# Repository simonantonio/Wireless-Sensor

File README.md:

Wireless Sensor Host Board
=========

This is a board used to implement wireless reporting of various sensors

Suggested Sensor Modules
---  

 - DHT22 - Temperature & Humidity  
 - TSOP4838 - IR Sensor (32khz carrier)  
 - Photo Resistor - Basic Light Levels  
 - Pulse Sensing - For use with hall effect sensors or weather stations such as [Spark Fun's Weather Station](https://www.sparkfun.com/products/8942)
 - BMP180 - Barometer & Temperature
 - Battery Voltage Monitoring
 
Results can then be transmitted to a receiver using a NRF24L01+ 

The board aims to be a low power long term sensor platform, potentially being powered from a LIPO battery directly or using a step down module such as the [Pololu Step Down Voltage Regulator](http://www.pololu.com/product/2097) 

Licensed Under the [Creative Commons Attribution-ShareAlike 3.0 Unported (CC-BY-SA 3.0)](https://creativecommons.org/licenses/by-sa/3.0/) and designed with the OSHW concepts in mind

 Intial Board Prototypes are being producted via the awesome service at [Dirty PCB's](http://dirtypcbs.com/)  
 Feel free to buy them [here](http://dirtypcbs.com/view.php?share=2637&accesskey=f92450b07b6b3961496835b5062594b2)  for $25.00USD

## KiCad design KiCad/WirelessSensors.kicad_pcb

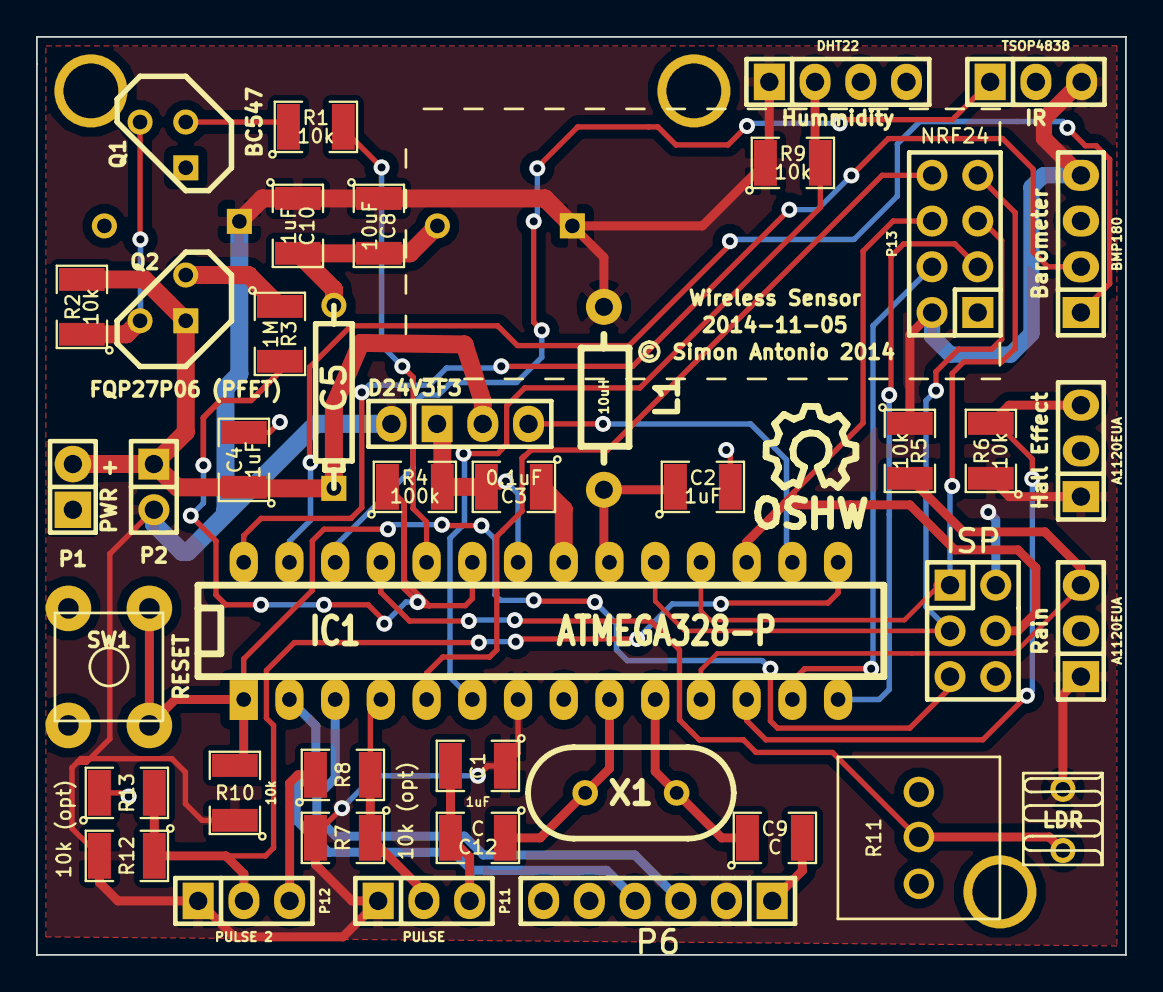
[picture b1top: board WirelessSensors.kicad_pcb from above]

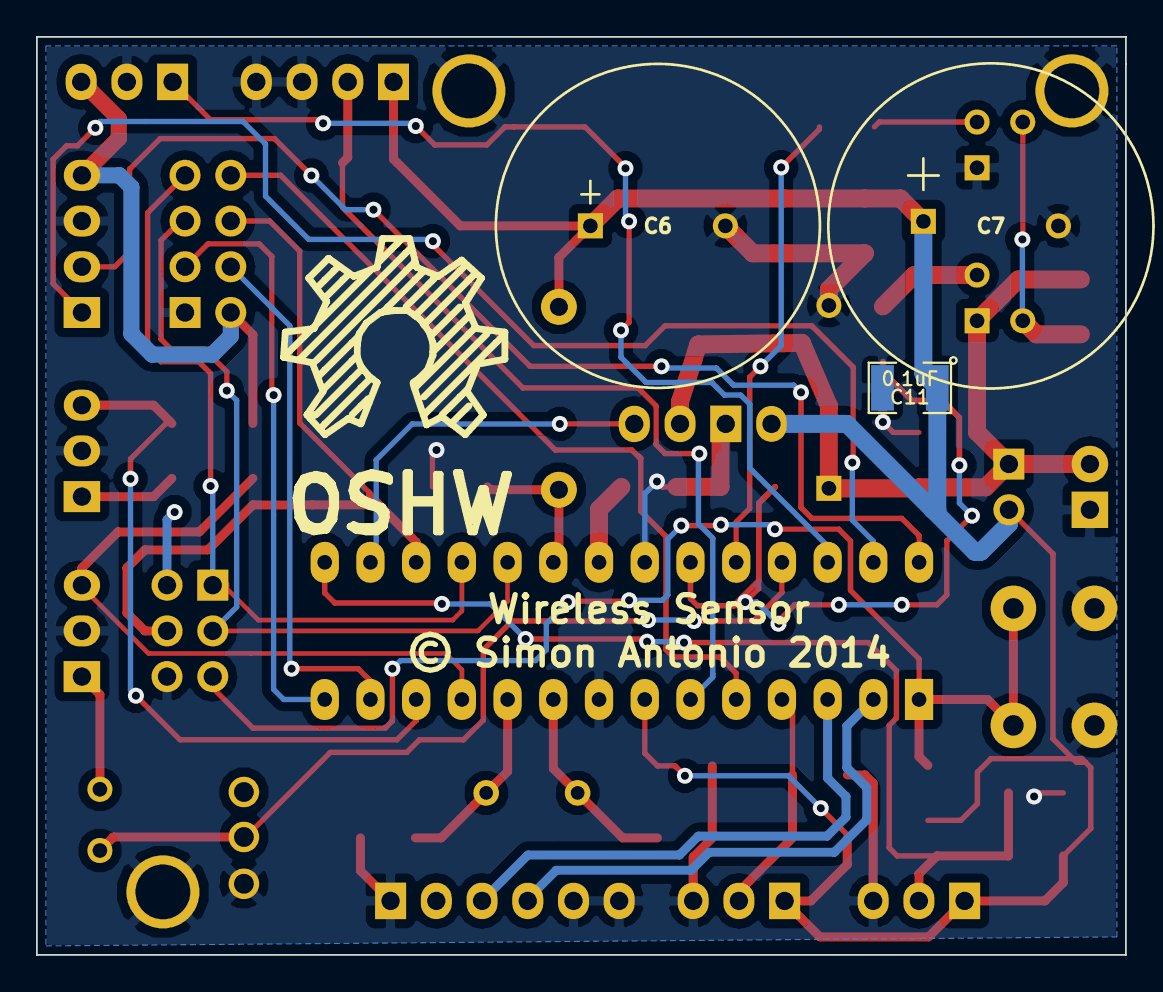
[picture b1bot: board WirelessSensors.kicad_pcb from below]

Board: 2 copper layers, 60.5 x 51.0 mm, 49 parts (4 on the bottom side), 31 nets.

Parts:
Barometer: BMP180; Pin_Header_Straight_1x04
C1, C2, C4, C10: 1uF; SMD-1210
C3, C11: 0.1uF; SMD-1210
C5: 1000uF; CP4
C6, C7: 4700uF; CP5
C8: 10uF; SMD-1210
C9, C12: C; SMD-1210
Hall Effect: A1120EUA; Pin_Header_Straight_1x03
Hummidity: DHT22; Pin_Header_Straight_1x04
IC1: ATMEGA328-P; DIP-28__300_ELL
IR: TSOP4838; Pin_Header_Straight_1x03
ISP: ISP; Pin_Header_Straight_2x03
L1: 10uH; Choke_Horizontal_RM10mm
Mount: P***; 1pin
Mount#2, Mount#3: P***; 1pin
P1: PWR +; Pin_Header_Straight_1x02
P2: PWR JMP; Pin_Header_Straight_2x01
P4: D24V3F3; Pin_Header_Straight_1x04
P6: External; Pin_Header_Straight_1x06
P11: PULSE; Pin_Header_Straight_1x03
P12: PULSE 2; Pin_Header_Straight_1x03
P13: NRF24; Pin_Header_Straight_2x04
Photoresister1: LDR; R1
Q1: BC547; TO92-123
Q2: FQP27P06 (PFET); TO92GSD
R1, R2, R5, R6, R9, R10, R11: 10k; SMD-1210
R3: 1M; SMD-1210
R4: 100k; SMD-1210
R7, R8, R12, R13: 10k (opt); SMD-1210
Rain: A1120EUA; Pin_Header_Straight_1x03
SW1: RESET; SW_PUSH
Sym: Symbol_OSHW-Logo_SilkScreen_BIG_07Jul2012; Symbol_OSHW-Logo_SilkScreen_BIG
X1: 8MHZ; HC-49V

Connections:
+3.3V: Barometer.4, C1.1, C6.1, C7.1, C8.1, C10.1, C11.1, Hall Effect.1, Hummidity.1, IC1.7, IR.3, ISP.2, L1.1, P2.2, P4.1, P6.2, P11.1, P12.1, P13.2, Photoresister1.1, R5.1, R6.1, R7.2, R9.1, R10.1, R12.2, Rain.1
/BAT_ADC: IC1.23, R3.2, R4.1
/BAT_MCU: IC1.24, R1.2
/DHT_MCU: Hummidity.2, IC1.6, R9.2
/HALL_MCU: Hall Effect.3, IC1.12, R6.2
/PHOTO_MCU: IC1.25, Photoresister1.2, R11.2
/PULSE2_MCU: IC1.15, P12.2, R12.1, R13.2
/PULSE_MCU: IC1.4, P11.2, R7.1, R8.2
/RAIN_MCU: IC1.11, R5.2, Rain.3
/SHDN: IC1.16, P4.4
/VIN: C4.1, C5.1, P1.2, P2.1, P4.3, Q2.S, R2.2
/XTAL1: C12.1, IC1.9, X1.2
/XTAL2: C9.1, IC1.10, X1.1
ADC3: IC1.26, IR.1
CE: IC1.14, P13.3
CSN: IC1.13, P13.4
GND: Barometer.3, C1.2, C2.2, C3.2, C4.2, C5.2, C6.2, C7.2, C8.2, C9.2, C10.2, C11.2, C12.2, Hall Effect.2, Hummidity.3, Hummidity.4, IC1.8, IC1.22, IR.2, ISP.6, Mount.1, Mount#2.1, Mount#3.1, P1.1, P4.2, P6.1, P6.5, P6.6, P11.3, P12.3, P13.1, Q1.3, R4.2, R8.1, R11.1, R13.1, Rain.2, SW1.2
IRQ: IC1.5, P13.8
MISO: IC1.18, ISP.1, P13.7
MOSI: IC1.17, ISP.4, P13.6
unnamed: C2.1, IC1.20, L1.2
unnamed: C3.1, IC1.21
unnamed: Q1.1, Q2.G, R2.1
unnamed: Q1.2, R1.1
unnamed: Q2.D, R3.1
RESET: IC1.1, ISP.5, R10.2, SW1.1
RX: IC1.2, P6.4
SCK: IC1.19, ISP.3, P13.5
SCL: Barometer.2, IC1.28
SDA: Barometer.1, IC1.27
TX: IC1.3, P6.3

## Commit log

2014-11-05 Add the KiCad project files
2014-11-05 Add Bill of Materials documentation
2014-11-05 Add Gerber files for production runs.
    Either via DirtyPCB's or SeeedStudio
2014-11-05 Added drill file
2014-11-05 Updated with 3 mounting holes.
2014-11-05 New mounting holes in pcb layout
2014-11-05 Updated Layout Gerbers
    Includes revision info and OSHW logo
2014-11-05 added additional details to PCB design
2014-11-05 Short Read Me added to briefly describe the project
2014-11-05 added licensing info to readme
2014-11-05 Board and Schematic Images
2014-11-05 Gerbers submitted to http://dirtypcbs.com/
2014-11-05 changed license to something more OSHW compatible, (CC-BY-SA 3.0)
2014-11-05 removed redundant text from readme
2014-11-05 Initial docs on board
2014-11-05 added Notes and Todo
2014-11-05 formatting
2014-11-05 more notes!
2014-12-03 Add initial commit of Arduino source code for Sensor Board
    FULLY UNTESTED and most certainly a WORK IN PROGRESS
2014-12-03 Add pin change interupt handling for Weather Station
2014-12-03 Trail version of a sloppy debounce method (no pin interrupts less than 500uS apart) will need to change this to be pin dependant.

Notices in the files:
KiCad/WirelessSensors.kicad_pcb:
© Simon Antonio 2014
